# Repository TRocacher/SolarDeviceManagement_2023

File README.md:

Ce dépôt, en construction, détaille la conception d'un système de pilotage de climatiseurs en fonction de l'excédent de puissance photovoltaïque pour une maison.
Le système s'appuie sur de l'existant :
- Climatiseurs (4) de type Mitsubishi 2kW
- un installation photovoltaïque avec un onduleur Fronius 6kVA SnapInverter associé à un smartMeter triphasé en point d'entrée de réseau ENEDIS

Le système va récupérer les informations de puissance produites par le SmartMeter (via l'onduleur et l'API REST Fournie par Fronius - req HTTP -  ) grâce à une 
carte Raspberry pi pour savoir si de la puissance est disponible.
Un réseau de capteurs est fabriqué (Hardware sous KiCad + Logiciel STM32L41 et STM32F103). Les capteurs communiquent en FSK 433MHz. Ces capteurs sont en fait
des Composants qui jouent le rôle de télécommande Infra Rouge afin de pouvoir commander chaque climatiseur et qui mesurent la température ambiante. Les codes IR
ont été obtenus en sniffant le signal transmis par les télécommandes d'origine.
Une passerelle est également construite, permettant d'échanger avec  les composants distants. Cette passerelle communique en UART avec la Raspberry pi. Cette dernière
hébergera un programme en Python avec une IHM sur écran tactile.
L'ensemble du projet est en cours de conception et réalisation, documenté en SysML pour avoir une vue d'ensemble (Caméo Modeler Magic Draw)
Mots clés : Logiciel embarqué C, Conception électronique, Routage KiCad, SysmL, Réseau de capteur, domotique,  ...

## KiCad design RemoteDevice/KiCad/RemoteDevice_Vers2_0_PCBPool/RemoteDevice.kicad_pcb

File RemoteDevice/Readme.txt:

/Dev_Soft_RemoteDevice_L031
Code du RmDv, progressif. Pour l'instant, code correspondant au test de durée Rentrée 2023

/Dev_Soft_ValidationRmDv_V2
Code de validation des modules RmDv version 2.0 PCB pool

TRES IMPORTANT !!
La carte 4IS gère mal le CD : pour que ça marche bien, il faut désactiver le carrier detect au niveau du module logiciel FSK.

CONFIGURATION EXCELLENTE EN QUALITE : 9600 Bds, Carte 4IS sans CD detect.
En 38400 + CD désactivé sur la carte IS = gros pépin de transmission (25%...)
-> essayer une transmission entre deux modules pour voir si l'élec HF est plus robuste que sur la carte 4IS ?

-> Test de validation 

**** CARTE n°1 OK ****
-Portée +++++ (portail / bureau 10/10)
- Prog :OK
- Reset :OK
- LED pushPull clignotant :OK
- Transm HF : OK 9600 dans les deux sens
- Test BP callback : Non fait, bug logiciel.

**** CARTE n°2 OK ****
- Portée moyenne
- Prog :OK
- Reset :OK
- LED pushPull clignotant :OK
- Transm HF : OK 9600 dans les deux sens
- Test BP callback : Non fait, bug logiciel.

**** CARTE n°3 ****
- Portée moyenne
- Prog :OK
- Reset :OK
- LED pushPull clignotant :OK
- Transm HF : OK 9600 dans les deux sens
- Test BP callback : Non fait, bug logiciel.

**** CARTE n°4 ****
- Portée moyenne
- Prog :OK
- Reset :OK
- LED pushPull clignotant :OK
- Transm HF : OK 9600 dans les deux sens
- Test BP callback : Non fait, bug logiciel.

**** CARTE n°5 ****
- Portée moyenne
- Prog :OK
- Reset :OK
- LED pushPull clignotant :OK
- Transm HF : OK 9600 dans les deux sens
- Test BP callback : Non fait, bug logiciel.

**** CARTE n°6 ****
-Portée ++++
- Prog :OK
- Reset :OK
- LED pushPull clignotant :OK
- Transm HF : OK 9600 dans les deux sens
- Test BP callback : Non fait, bug logiciel.

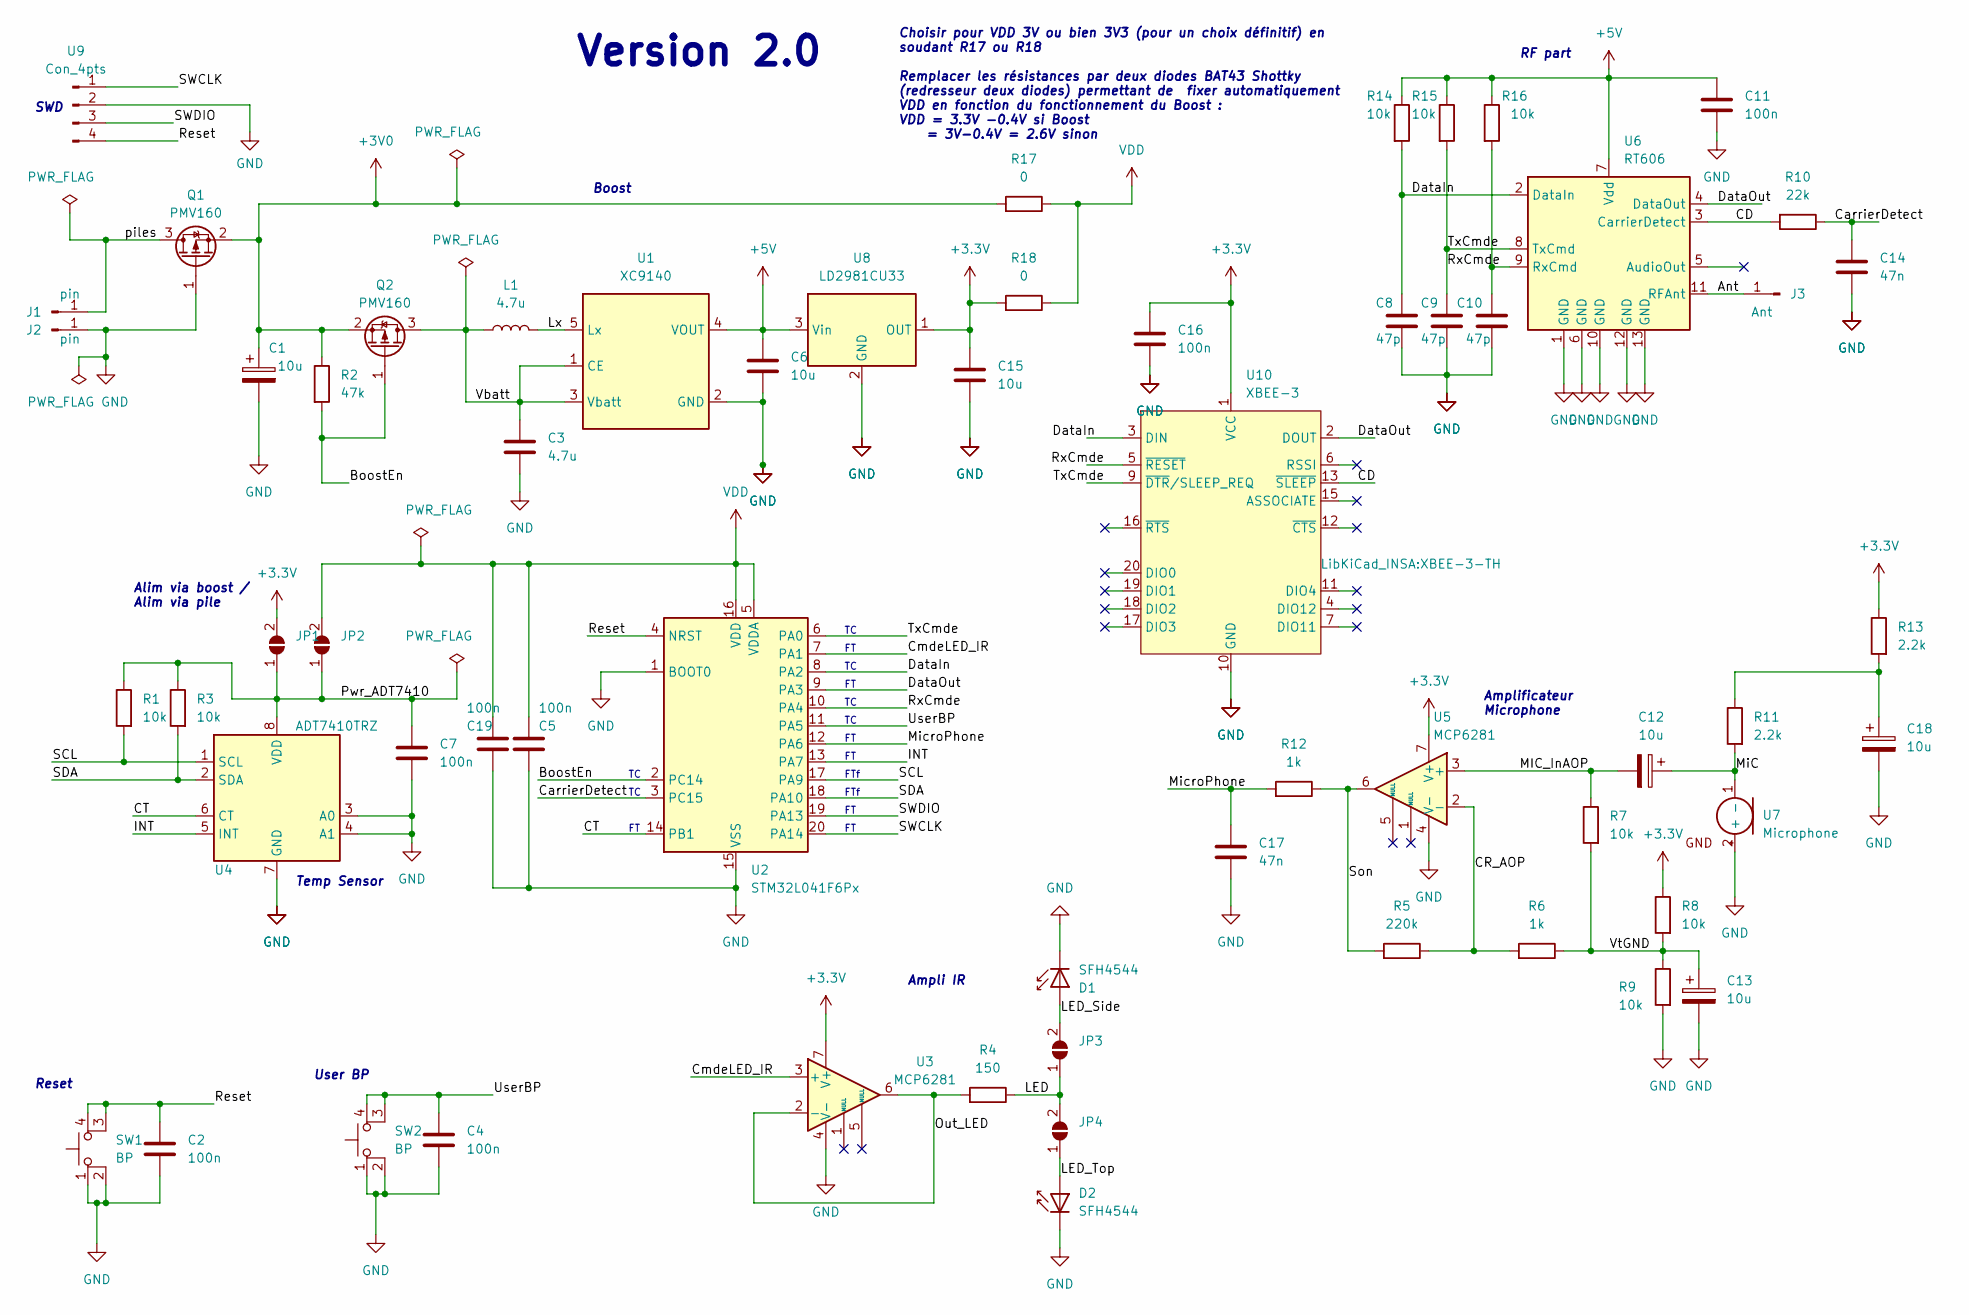
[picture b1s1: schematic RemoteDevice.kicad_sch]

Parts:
C1, C12, C13, C18: 10u; CP_EIA-7132-20_AVX-U
C2, C4, C5, C7, C11, C16, C19: 100n; C_1206_3216Metric
C3: 4.7u; C_1812_4532Metric
C6, C15: 10u; C_1812_4532Metric
C8, C9, C10: 47p; C_0805_2012Metric
C14, C17: 47n; C_1206_3216Metric
D1, D2: SFH4544; LED_D5.0mm_IRGrey
J1, J2: pin; PinHeader1Pt
J3: Ant; PinHeader1Pt
JP1, JP2, JP3, JP4: SolderJumper_2_Open; SolderJumper-2_P1.3mm_Open_TrianglePad1.0x1.5mm
L1: 4.7u; L_Abracon_ASPI-3012S
Q1, Q2: PMV160; SOT-23
R1, R3, R7, R8, R9, R14, R15, R16: 10k; R_1206_3216Metric
R2: 47k; R_1206_3216Metric
R4: 150; R_1206_3216Metric
R5: 220k; R_1206_3216Metric
R6, R12: 1k; R_1206_3216Metric
R10: 22k; R_1206_3216Metric
R11, R13: 2.2k; R_1206_3216Metric
R17, R18: 0; R_1206_3216Metric
SW1, SW2: BP; SW
U1: XC9140; SOT-23-5
U2: STM32L041F6Px; TSSOP-20_4.4x6.5mm_P0.65mm
U3, U5: MCP6281; SOIC-8_3.9x4.9mm_P1.27mm
U4: ADT7410TRZ; SOP-8_3.9x4.9mm_P1.27mm
U6: RT606
U7: Microphone
U8: LD2981CU33; SOT-89-3_Handsoldering
U9: Con_4pts; PinHeader4pts
U10: XBEE-3; XBEE-3-TH

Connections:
+3V0: C1.1, Q1.2 (S), Q2.2 (S), R2.1, R17.2
+3V3: C15.1, C16.1, JP1.2 (B), R8.1, R13.1, R18.2, U3.7 (V+), U5.7 (V+), U8.1 (OUT), U10.1 (VCC)
+5V: C6.1, C11.1, R14.1, R15.1, R16.1, U1.4 (VOUT), U6.7 (Vdd), U8.3 (Vin)
/Ant: J3.1, U6.11 (RFAnt)
/BoostEn: Q2.1 (G), R2.2, U2.2 (PC14)
/CD: R10.2, U6.3 (CarrierDetect), U10.13 (~SLEEP)
/CR_AOP: R5.1, R6.2, U5.2 (-)
/CT: U2.14 (PB1), U4.6 (CT)
/CarrierDetect: C14.1, R10.1, U2.3 (PC15)
/CmdeLED_IR: U2.7 (PA1), U3.3 (+)
/DataIn: C8.1, R14.2, U2.8 (PA2), U6.2 (DataIn), U10.3 (DIN)
/DataOut: U2.9 (PA3), U6.4 (DataOut), U10.2 (DOUT)
/INT: U2.13 (PA7), U4.5 (INT)
/LED: JP3.1 (A), JP4.2 (B), R4.1
/LED_Side: D1.2 (A), JP3.2 (B)
/LED_Top: D2.2 (A), JP4.1 (A)
/Lx: L1.1, U1.5 (Lx)
/MIC_InAOP: C12.2, R7.1, U5.3 (+)
/MiC: C12.1, R11.2, U7.1 (-)
/MicroPhone: C17.1, R12.2, U2.12 (PA6)
/Out_LED: R4.2, U3.2 (-), U3.6
/Pwr_ADT7410: C7.1, JP1.1 (A), JP2.1 (A), R1.1, R3.1, U4.8 (VDD)
/Reset: C2.1, SW1.3, SW1.4, U2.4 (NRST), U9.4
/RxCmde: C10.1, R16.2, U2.10 (PA4), U6.9 (RxCmd), U10.5 (~RESET)
/SCL: R1.2, U2.17 (PA9), U4.1 (SCL)
/SDA: R3.2, U2.18 (PA10), U4.2 (SDA)
/SWCLK: U2.20 (PA14), U9.1
/SWDIO: U2.19 (PA13), U9.3
/Son: R5.2, R12.1, U5.6
/TxCmde: C9.1, R15.2, U2.6 (PA0), U6.8 (TxCmd), U10.9 (~DTR/SLEEP_REQ)
/UserBP: C4.1, SW2.3, SW2.4, U2.11 (PA5)
/Vbatt: C3.1, L1.2, Q2.3 (D), U1.1 (CE), U1.3 (Vbatt)
/VtGND: C13.1, R6.1, R7.2, R8.2, R9.1
/piles: J1.1, Q1.3 (D)
GND: C1.2, C2.2, C3.2, C4.2, C5.2, C6.2, C7.2, C8.2, C9.2, C10.2, C11.2, C13.2, C14.2, C15.2, C16.2, C17.2, C18.2, C19.2, D1.1 (K), D2.1 (K), J2.1, Q1.1 (G), R9.2, SW1.1, SW1.2, SW2.1, SW2.2, U1.2 (GND), U2.1 (BOOT0), U2.15 (VSS), U3.4 (V-), U4.3 (A0), U4.4 (A1), U4.7 (GND), U5.4 (V-), U6.1 (GND), U6.6 (GND), U6.10 (GND), U6.12 (GND), U6.13 (GND), U7.2 (+), U8.2 (GND), U9.2, U10.10 (GND)
unnamed: C18.1, R11.1, R13.2
VDD: C5.1, C19.1, JP2.2 (B), R17.1, R18.1, U2.5 (VDDA), U2.16 (VDD)

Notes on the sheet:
FTf
Ampli IR
Boost
Reset
RF part
Alim via boost / Alim via pile
Amplificateur Microphone
Choisir pour VDD 3V ou bien 3V3 (pour un choix définitif) en soudant R17 ou R18 Remplacer les résistances par deux diodes BAT43 Shottky (redresseur deux diodes) permettant de fixer automatiquement VDD en fonction du fonctionnement du Boost : VDD = 3.3V -0.4V si Boost = 3V-0.4V = 2.6V sinon
Temp Sensor
Version 2.0
User BP
SWD

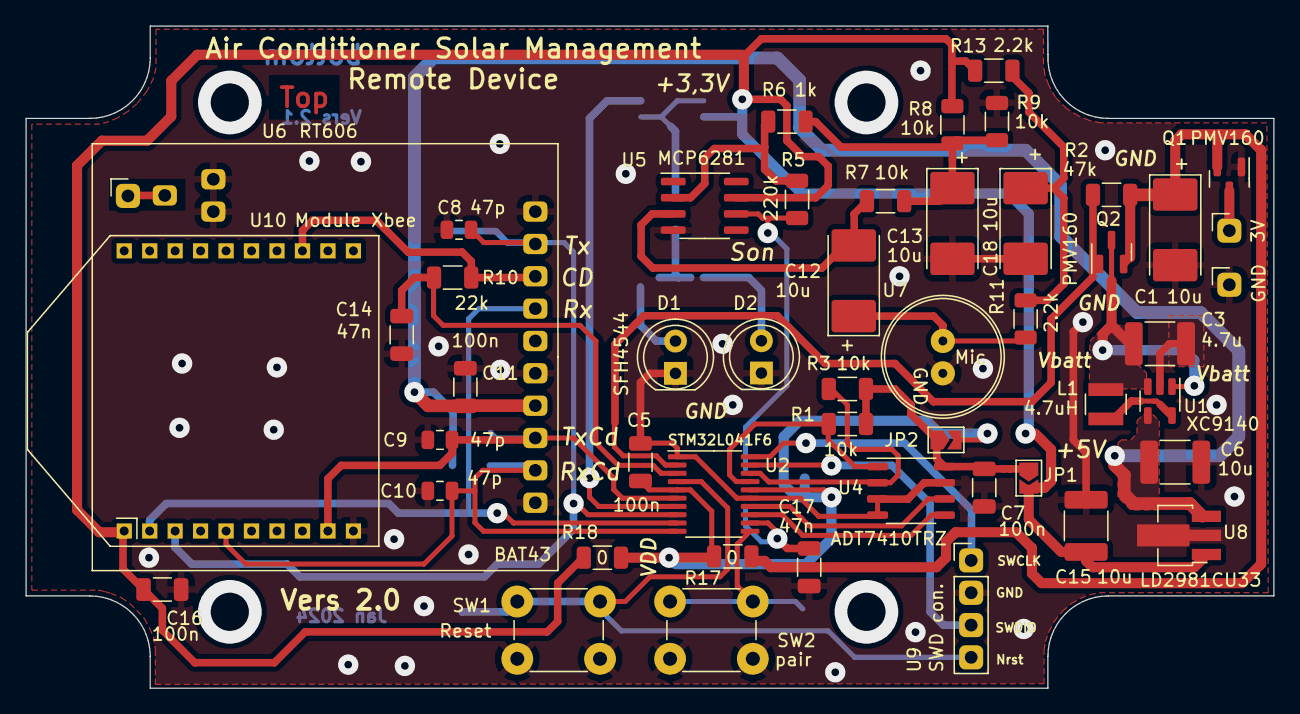
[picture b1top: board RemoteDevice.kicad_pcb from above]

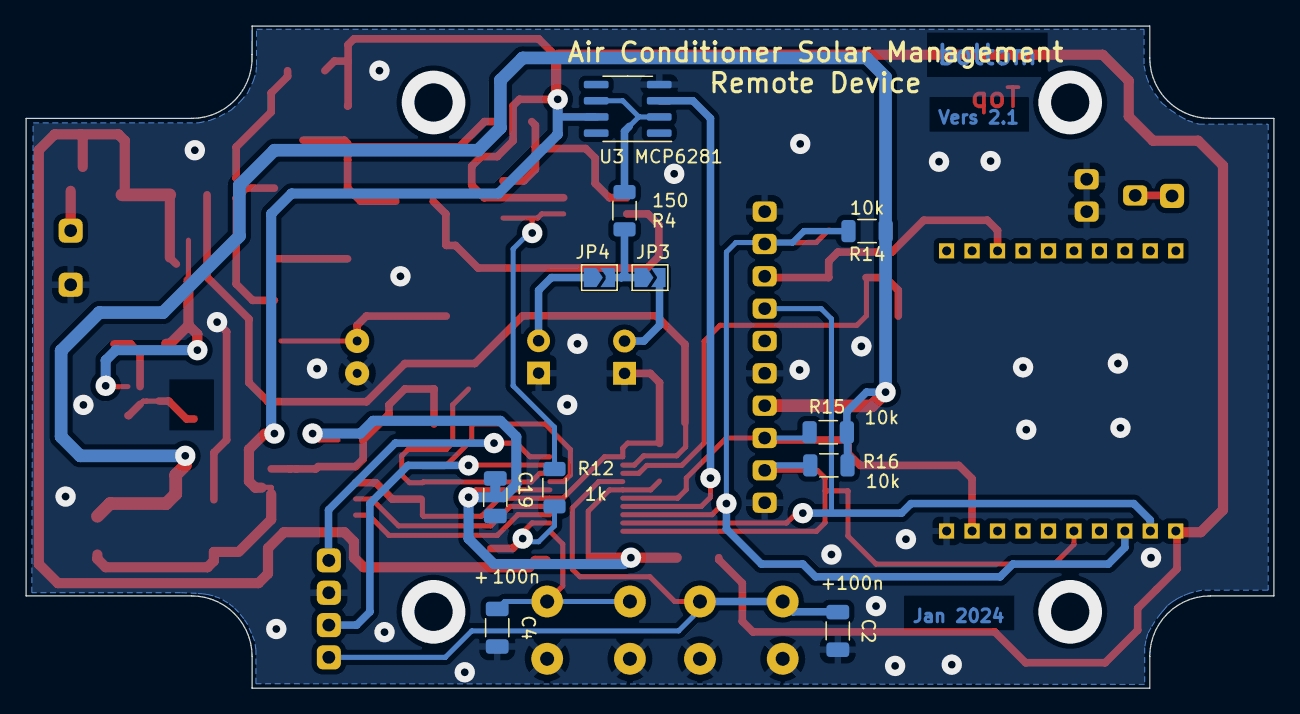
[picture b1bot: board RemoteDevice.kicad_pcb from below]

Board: 2 copper layers, 98.0 x 52.0 mm, 61 parts (11 on the bottom side), 37 nets.

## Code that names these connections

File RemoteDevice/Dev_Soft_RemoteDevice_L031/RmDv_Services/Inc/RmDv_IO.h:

/*
 * RemoteDevice_IO.h
 *
 *  Created on: Jul 3, 2022
 *      Author: trocache
 */
#include "stm32l0xx_ll_bus.h"
#include "stm32l0xx_ll_gpio.h"
#include "GPIO_L031.h"
#ifndef INC_RMDV_IO_H_
#define INC_RMDV_IO_H_


/*
 *                  STM32L041F6P7 / STM32L031F6P7  / TSSOP 20
 *           _________________________________________
 * 			|                                         |
 *      -->-|Boot0                           PA14 SWCK|----
 *      --<-|Boost_En PC14 (OD)             PA13 SWDIO|----
 *      -->-|CD PC15                     (OD) PA10 SDA|-><-
 *      -->-|nRST                        (OD) PA9  SCL|->--
 *      ->>-|VDDA                                  VDD|-<<-
 *      --<-|TxCmde PA0 (OD)                       VSS|-<<-
 *      --<-|LED_IR PA1 (PPUL)                  PB1 CT|-<--
 *      --<-|Tx PA2 (OD)                       PA7 INT|-<--
 *      -->-|Rx PA3                (analog)PA6 ADC in6|-<--
 *      --<-|RxCmde PA4 (OD)       (pull up)PA5 UserBP|-<--
 *          |_________________________________________|
 *
 *
 *
 *
 *
 */

#define nBoost_En_Pin LL_GPIO_PIN_14
#define nBoost_En_GPIO_Port GPIOC
#define CD_Pin LL_GPIO_PIN_15
#define CD_GPIO_Port GPIOC
#define TxCmde_Pin LL_GPIO_PIN_0
#define TxCmde_GPIO_Port GPIOA
#define LED_IR_Pin LL_GPIO_PIN_1
#define LED_IR_GPIO_Port GPIOA
#define RxCmde_Pin LL_GPIO_PIN_4
#define RxCmde_GPIO_Port GPIOA
#define User_BP_Pin LL_GPIO_PIN_5
#define User_BP_GPIO_Port GPIOA
#define INT_Pin LL_GPIO_PIN_7
#define INT_GPIO_Port GPIOA
#define CT_Pin LL_GPIO_PIN_1
#define CT_GPIO_Port GPIOB

#define RmDv_IO_Prio_UserBP 2
void RmDv_IO_Init(void);
void RmDv_IO_AssociateFct_UserBP(void (*IT_function) (void));

#endif /* INC_RMDV_IO_H_ */

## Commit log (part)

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2022-12-03 Reprise propre du pojet. Voir Alire.txt. Tout le travail précédent est dans ../Back
2022-12-04 démarrage SysML. Le premier use case est fait, le diag de seq de base est également construit. Poursuivre
2022-12-04 Bdd et ibd remote device OK. Reste à faire le diagramme de classe
2022-12-11 Le fichier attaché est un odt, donc dynamique. Les messages de com sont faits, les diag de séquences aussi (pairing et run), l'architecture logicielle com peut commencer....
2022-12-15 Idée nouvelle, qui s'inspire des couches OSI.... pas gagné
2022-12-30 Systeme : Grosse avancée sur l'architecture de la pile de communication. L'odt est bien parti mais il faut l'avancer rapidement
2023-01-03 Système : avancement de la pile, attaquer les FSM de la couche exchandeCtrl...
2023-01-05 Système : FSM Request et FSM Asynchronuous message faits. Reste à rédiger celui de réception
2023-01-08 Système : attention, pb avec ExchInde, remplacé par ID dans la frame et on ajoute Index local pour l'échange voir p21. Réécriture...
2023-01-21 Système : première étape imprimée. Deux fichiers séparés, LaPile_FSK_COM_Stack.odt et Description.odt. Relecture papier en cours
2023-01-22 Système : FSM démarrées sur MAC et PhyUART. Next step, démarrer le code cube
2023-01-26 Systeme + Stack : Phy testé avec XCTU sur COM1. Len error, Timeout, normal, validés. A faire : le checksum
2023-01-29 System+Stack : Phy_UART, FSM de réception validé avec XCTU sur COM1. Voir rep TestDeValidation/X_CTU_Test_1. Finaliser les fcts d'interface avec MAC
2023-01-30 System + Stack 103 : chronométrage faits, mise au propore sur odt. Test em/rec Master vers XCTU via FSK OK. A faire : coder un Slave pour test portée
2023-02-01 System+Stack : PB slave/master. Possible plantage car émission/réception pas clairement exclusif. Tentative FSM amélioré branche Test_Stack
2023-02-01 Stack : version SendMessg fusionné dans la FSM. Code Master revu. Tester !
2023-02-04 System+Stack : on décale la détection du header dans l'IT UART de manière à soulager la scrutation de la FSM Phy_UART
2023-02-04 System+Stack : voir odt pour la nouvelle version. Le code est à poursuivre, grand ménage sur les répertoires
2023-02-05 System + Stack bien débuggé, reste : vérifier calcul différence TimeOut, mettre les priorité en define, tester le filtrage CD
2023-02-05 System+stack : OK validation diff Timeout, prio en define et filtrage CD OK sur test 1 (à durcir)
2023-02-13 System+Stack : débugg de la détection porteuse, CD. Il ne faut pas gérer les IT via RXNE ou NVIC, il faut juste neutraliser la réception
2023-02-15 System+Stack : les .h sont commentés, un user guide concernant la stack est commencé, OK pour la couche physique. Passer à la MAC
2023-02-18 System + Stack : reprise commit Master n def487e. Développement MAC ne modifiant / ajoutant des fct dans la lib PhyUART nommée maintenant MACPhyUART
2023-02-19 System+Stack : MAC presque finie, broadcast OK, pb erreur overrun réglé, doc de conception à continuer, test aux longueurs limites à faire
2023-02-20 System + Stack : MAC OK, User Guide fait !
2023-02-21 System+Stack : démarrage de la couche Exchange, poursuivre la FSM de bas niveau
2023-02-25 System + Stack : version néttoyée, Stack limitée à la couche MAC. Odt de conception et UG à jour, SysML limité à MAC
2023-02-26 System + Stack : version FSK et UART dans deux fichiers séparés. Renommage des fichiers drivers avec l'extension _F103
2023-03-04 Menu : le document de conception est avancé. On fait une pause pour explorer l'écran tactile...
2023-07-15 UC : ajout d'un doc de conception odt. Partie écran tactile difficile, traitée dans /formation, autre dossier, sysml avancé
2023-07-16 Soft : Demarrage développement Remote Device. Software, architecture démarrée, SysML modifié, cible STM32L031
2023-07-22 Soft : I2C en cours, niveau registre, en DMA. Ne fonctionne pas encore. Le code initalise les IO en désactivant le boost (donc peu de puissance)
2023-07-25 Soft : Ecriture et lecture passent, mais les données relues sont aberrantes. Ajouter la stack et modifier la tempo, à ajouter après allumage 7410
2023-07-26 Soft : DMA et scrutation OK. Fonctionnait depuis le départ mais mauvaise utilisation avec le slave git status
2023-07-26 Soft : température OK version registre, scrutatif ou DMA. Lecture en float, température négative gérée dans le main de démo
2023-07-26 Soft : lecture température qui plante si on ne mets pas l'init 7410 ds la boucle. A débugger. SysML à jour Diag classe SysML
2023-08-15 System + stack : la doc pile est bien avancée, soft pile juste avant restructuration logicielle (diag classe)
2023-08-16 System+Stack : la version 103 est restructurée, nouveau diag de classe SysML, UG presque fini, travail fait sous KEIL, rien n'est testé git add --all
2023-08-18 System + Stack : la version restructurée pour STM32F103 de la pile est testée sur le test 3, ping pong. OK
2023-08-18 System + Stack : le UG est terminé pdf, la pile est validée ping pong avec le RmDevice (donc STM32L031), taux d'erreur plus important que sur le 103, inexpliqué. Mais OK. SysML pile Ok.
2023-08-19 Soft Led Clim : l'ancienne version cmdeClim sous Cube IDE et pour un 103 est ajouté. Testé OK. Il faut le documenter et le faire migrer vers le L031
2023-08-26 Remote Device. Révision bug I2C. OK avec en plus timeout intégré dans driver I2C. Test Stack OK moins d'erreur. Modif Timer.c pour éviter de reinitialiser le systick s'il l'a déjà été
2023-08-27 Soft : mesure temp avec exclusion min max et moyenne sur deux valeurs. I2C OK en DMA et scrutation nickel. A suivre low power
2023-08-29 Soft : LPTIM OK, va permettre de générer un Wdog régulier pour sortir le RmDv d'une situation de plantage. Test LED ttes les 5 sec OK
2023-08-29 Soft : LE SYSTICK avait un soucis au démarrage. Réglé, mais tester les timeout. Le LPTIM est OK
2023-08-30 Soft : pgm avancée mais pas mal de bug, dont transmission à revoir
2023-09-01 Soft : avancement projet RmDv, encore un bug sur le comptage réception à régler sous KEIL
2023-09-02 Soft : code RmDv OK, mes temp, send temp, recep Code clim, activer clim, sleep stby 2mn en fait 1m45. UC affiche temp, compte réveil RmDv. Pourquivre voir Conception RmDv ToDo. Test d'endurance pile
2023-09-09 Soft : émission multiple avec TimeOut au niveau couche protocole ajoutée et validée.
2023-10-12 modifs non détaillées....
2023-10-12 Soft : Projet PowerMeter pret a etre developpe. ADC a faire en prio
2024-01-10 Avancement SysML au niveau des inchanges entre les sous-systèmes. Creation du fichier qui accompagne le SysML, Systeme_CommunicationIntra.odt
2024-01-11 MODIFICATION PROFONDE des dénominations de la pile HF, elle s'appelle maitenant FSKStack. Les noms de fcs sont revus. Le projet RmDv se compile. Celui côté Gateway aussi. En principe ça tourne , mais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
2024-01-21 système repensé avec la gestion centralisé dans la Gateway. Pgm SmartGateway commencé, avec la gestion des timestamps. Réflexion aussi sur l'échange de donnees via UART avec écriture directe dans une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
2024-01-24 UART de py vers SGw OK avec format nb bytes, data. Pensé en IT avec Timeout. OK réel. Faire la partie checksum. Horodatage très avancé.
2024-01-29 Avancement SGw....
2024-01-30 Demarrage des procédure de validation. nveau rep /Dev_Soft/ValidationRmDv_V2 contient le code de validation des 6 RmDv V2.0. Le readme indique la progression des tests par carte
2024-01-30 Transfert Raspy vers UC, format heure. La transmission série avec checksum est OK. A poursuivre proprement. Archi Python en odt et SysML avancé
2024-02-01 Mise à jour du code KEIL Espion avec les nouveaux noms de fichiers de la pile. Le RmDv n°1 est OK. Test nickel en 9600Bds, pas de CD detecte côté UC Espion
2024-02-04 Fichier odt avancé, on précise les modes de fonctionnement ainsi que les params
2024-02-04 Les 6 cartes sont validées. Dans le Readme une comparaison des portées de chaque RmDv est donnée. A faire : essayer une liaison entre deux RmDv pour voir si la détection CD est plus efficace que sur 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
2024-02-19 communication avec l'IHM OK : toutes les datas sont mises à jour en même temps. Tourne avec l'appli Python git num 36a75ef+1. A épurer pour se projeter vers l'appli finale
2024-02-21 Version avec structure de données centrale revisitée
2024-02-28 SGw revue sur l'aspect communication RmDv : protocole modifié, renommé. code qui merge IHM avec avancement max + comm RmDv. A tester
2024-02-29 Debug Wireless : simplex RmDv vers SGw OK 9600Bds sans CD au niveau de SGw (carte réseau capteur)
2024-02-29 Debug Wireless: Timeout validé. Description, dans l'IT 1sec, on procède à deux autres émissions à 250ms d'intervalle via le timeout
2024-02-29 Debug Wireless : nouvelle fonction dans la couche protocole permettant d'envoyer la req info avec timeout et essais multiples : OK
2024-03-01 Debug Wireless: requête info et requête status OK, 3 tentatives
2024-03-01 Debug Wireless : requête info + status, timeout OK, portée vérifée. Première release du code RmDv
2024-03-18 improve RmDv:gestion délai via bkpreg_1 OK côté RmDv. Le nouveau délai est obtenu à partir de celui reçu + 2sec. Sur ce test, KEIL renvoie un délai de 65535 donc un bricolage est fait pour mettre à j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
2024-03-26 Improve RmDv : la gestion du timing est OK mais visiblement une DLL se cache derrière. Pas du tout évident ce réglage. Voir si on abandonne ou si on trouvequelque chose de plus simple
2024-03-31 Improve SGw : On change la stratégie PLL et on part sur un tableau de prévision toutes les 30mn (scheduler) avec un index qui est inc toutes les 30mn avec un shift de 15mn. Le test d'incrémentation t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
2024-04-07 Improve Sync RmDv-SGw: ping pong 30 secondes (non précis) OK. Insertion Transaction Idx dans les échanges, donc modifs Protocole. Mettre en place l'utilisation du tableau. Simplifier la structure RmDv
2024-04-09 Improve Sync RmDv-SGw : fait, non testé. Pose pas mal de soucis au débugage. Provisoirement abandonné pour repartir sur une version sans fuseaux h.
2024-04-10 improve Sync Time : Version OK entre RmDv et SGw. Il y avait un GROS BUG au niveau RmDv (mise à jour RTC au mauvais moment). Fait avec un test toutes les 60 secondes avec compensation : OK nickel !
2024-04-15 Improve Synch Time : Bug revu RmDv, maintenant on peut correctement ajuster la RTC à 1 seconde. A faire : décaler de 5 secondes par exemlpe toutes les clim pour pas qu'il y ait de bourrage. Côté RmDv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
2024-04-20 Improuve SGw : échelonnage 5sec fait, à tester. Finaliser code propre RmDv à faire...
2024-04-21 RmDv + SGw : les RmDv sont revus, le code est propre. Pas de pilotage Clim pour l'instant (juste une incrémentation du set de température). Le SGw tourne avec undécalage de 5 secondes pour chaque RmD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
2024-04-27 SGw : ajout d'un antirebond sur BpUser + récup de toutes les IT système, comme Fault et affichage LCD. Bug SGw en stand alone sur prise idpt non reproductible en débugg in situ... A voir, Alim ?
2024-04-29 RmDv OK, ajout des fct enable disable bkpReg. Ensemble qui permet de valider la cmde des clim avec consigne donnée par le SGw via UserBP
2024-05-01 RmDv: V.1.00, SGw : a.0. Ajout des fonctionnalités d'information version Code. Prêt pour reprise Raspy HMI...
2024-08-21 Ajout doc gestion tps, SGw avancee ajout Algo HMI programmation, ajout affichage LCD lors de plantage while 1
2024-08-23 Version 1.01, HMI et RmDv fonctionnent bien ensemble. Périodiser requête côté HMI. Poursuivre développement LCD voir SGw_UG.odt
2024-08-29 Version 1.02: LCD OK, tester la fonctionnalité no beep, donc revoir aussi soft Rmdv. Voir petit suivi...
2024-10-09 Mise à jour des version 1.01 remote device et 1.04 pour SmGw, validation des mises à jour et développements précédents
2024-10-10 SmGw version 2.00, mise à jour pour le compilateur Keil V6. Modif indiquées sur le fichier txt de révision. Fonctionnement OK
2024-10-15 algo Automatique bien avancé, mais absolument pas testé. A poursuivre avec rigueur et à tester...
2024-10-17 SGw Vers 2.01: premiers débuggage en reel mais en simulant les données de Puissance en excès, voir odt dans System. A poursuivre
